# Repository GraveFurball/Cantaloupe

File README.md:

# The Cantaloupe
Yet another star configuration CAN PCB for FRC

The Cantaloupe is yet another PCB to enable an FRC CAN Bus to be laid out in a star topography. 
The Cantaloupe was inspired partially by FRC 6502's board, [the CANTina](https://github.com/21brownz/CANtina)
* The Cantaloupe utilizes Weidmuller LSF-SMT-3.5 push-to-connect terminal blocks to allow you to easily connect and disconnect devices.
* The Cantaloupe has the capacity for up to 20 CAN devices simultaneousely.
* The Cantaloupe has built in mounting holes for #4 screws, as well as holes intended for running zipties through to aid in cable management.
* The Cantaloupe has a built in jumper, allowing you to choose whether or not to terminate the CAN bus on the board.
* The hardware that we used to assemble the Cantaloupe is contained within the "Hardware" file.

## Warning:
Star topology can be very fussy. It violates the ISO 11898 standard and is not officially supported by any manufacturer. I do not officially condone the use of star configuration, nor do I accept any responsibility in the event that star CAN causes damage to one or more of your CAN devices. **Please be careful!**

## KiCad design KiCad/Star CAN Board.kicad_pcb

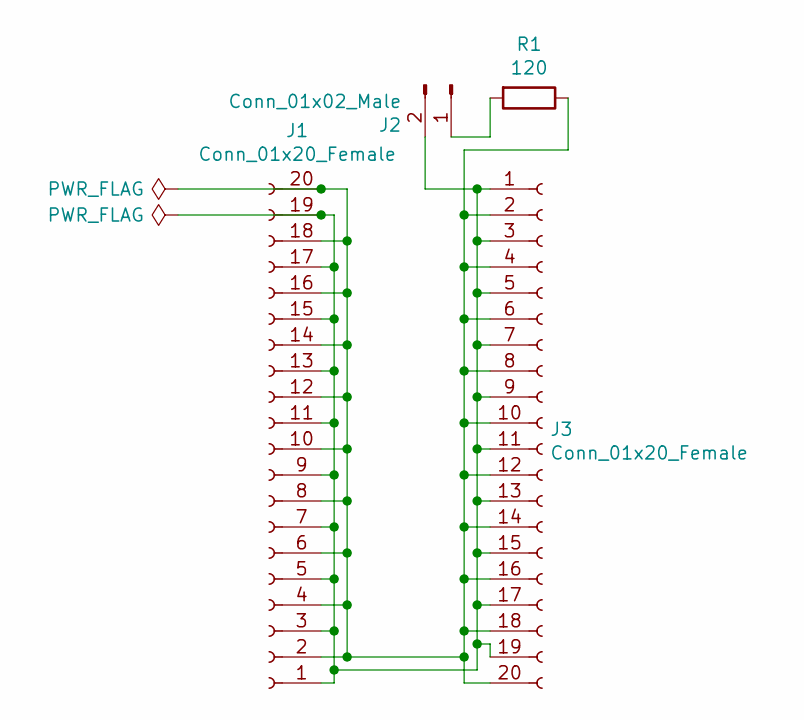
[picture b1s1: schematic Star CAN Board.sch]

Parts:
J1, J3: Conn_01x20_Female; Weidmuller20X1Female
J2: Conn_01x02_Male; PinHeader_1x02_P2.54mm_Vertical
R1: 120; R_Axial_DIN0207_L6.3mm_D2.5mm_P10.16mm_Horizontal

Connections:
unnamed: J1.1, J1.3, J1.5, J1.7, J1.9, J1.11, J1.13, J1.15, J1.17, J1.19, J2.2, J3.1, J3.3, J3.5, J3.7, J3.9, J3.11, J3.13, J3.15, J3.17, J3.19
unnamed: J1.2, J1.4, J1.6, J1.8, J1.10, J1.12, J1.14, J1.16, J1.18, J1.20, J3.2, J3.4, J3.6, J3.8, J3.10, J3.12, J3.14, J3.16, J3.18, J3.20, R1.1
unnamed: J2.1, R1.2

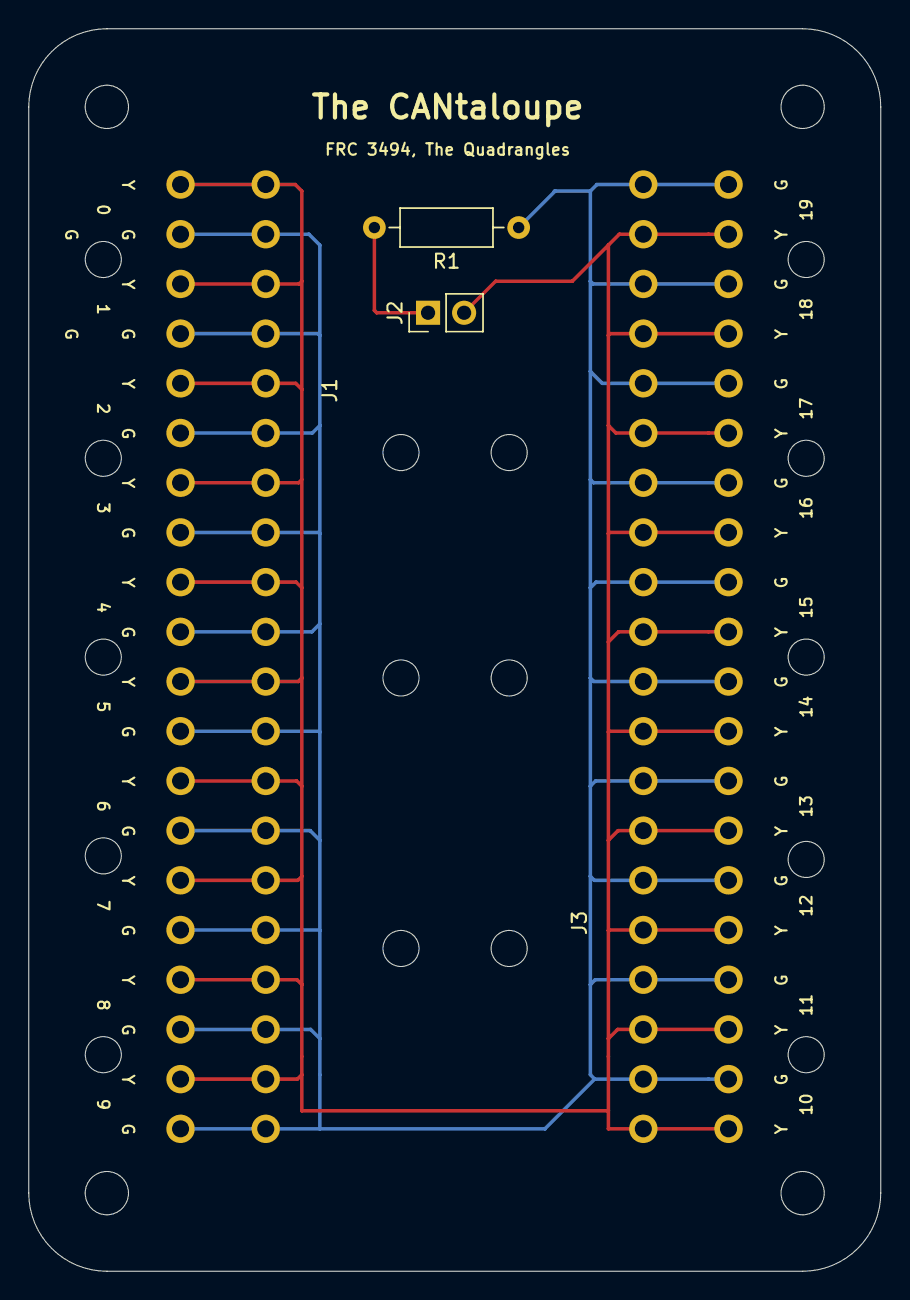
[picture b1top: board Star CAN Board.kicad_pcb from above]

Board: 2 copper layers, 60.0 x 87.5 mm, 4 parts (0 on the bottom side), 3 nets.

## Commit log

2019-12-30 Added image
2019-12-30 Fixed image name bc I am bad at git
2019-12-30 Reorganized
2020-02-18 hi this is FizzyApple12 pushing stuff for GraveFurball ok bye
2020-03-01 Removed link for old resistor
    New design uses a generic 1/4 watt through-hole resistor rather than an smd resistor, so the link is no longer useful
2020-04-09 Updated picture to V1.1
2020-04-09 Added a link for a resistor of the same type that we used
2020-04-09 Made links into a .md
2020-04-09 Updated Hardware file
    Added link to pin headers, also added notes with more information about substitutes.
2020-04-09 Update README.md
    Changed name of "links" to match the new "hardware" name, fixed some grammar here and there
